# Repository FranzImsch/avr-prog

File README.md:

# AVR-Prog
Basic Programmer for AVR-Chips. It's based off the [Sparkfun Tiny AVR Programmer](https://github.com/sparkfun/Tiny-AVR-Programmer).

Features are:
- USB-C connector,
- 5V or 3V3 logic level,
- Tag-Connect connector.

## Partlist

|Name     |Component             |Package                |
|---------|----------------------|-----------------------|
|C1, C3   |100nF Cap             |0603                   |
|C2       |10µF Cap              |0603                   |
|C4, C5   |2.2µF Cap             |0603                   |
|C6, C9   |18pF Cap              |0603                   |
|IC1      |ATTINY84A-SSU         |SOIC127P600X175-14N    |
|J1       |JUMPER 3x 1.27mm      |                       |
|J3       |Box Header 6P         |                       |
|LED      |LED                   |0603                   |
|R1       |1K Resistor           |0402                   |
|R2, R9   |68Ω Resistor          |0402                   |
|R3       |1K5 Resistor          |0402                   |
|R4       |10KΩ Resistor         |0603                   |
|R6, R7   |5K1 Resistor          |0402                   |
|R8       |10K Resistor          |0402                   |
|U$1      |USB-C Connector       |TYPE-C16PIN            |
|U$2      |TLV75533PDBVR         |SOT23-5                |
|U$3      |SRV05-4-P-T7          |SOT23-6                |
|X1       |KMD160001210          |M-49USSMD              |

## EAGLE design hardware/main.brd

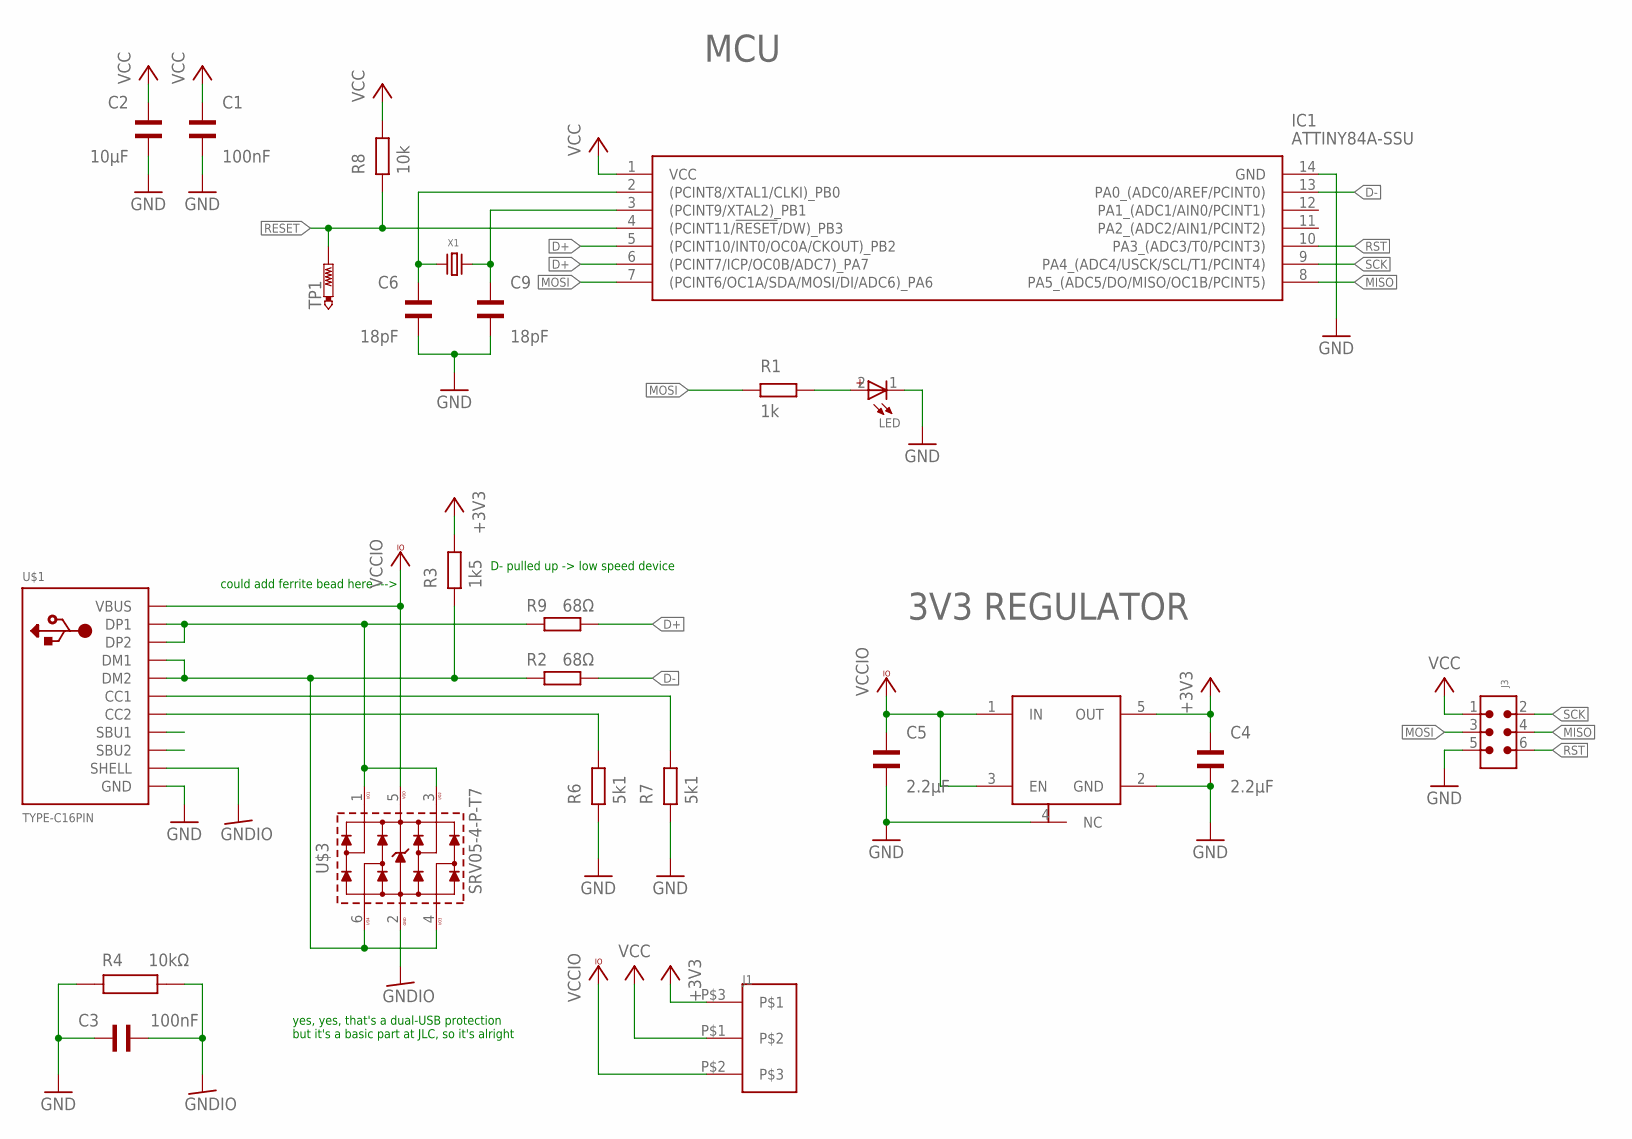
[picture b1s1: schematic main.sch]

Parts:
C1, C3: 100nF; WCAP-CSGP_0603_REFLOW
C2: 10µF; WCAP-CSGP_0603_REFLOW
C4, C5: 2.2µF; WCAP-CSGP_0603_REFLOW
C6, C9: 18pF; WCAP-CSGP_0603_REFLOW
IC1: ATTINY84A-SSU; SOIC127P600X175-14N
J1: JUMPER1.27; 1.27_JUMPER
J3: 6120XX21621_61200621621; 61200621621
LED: WL-SMCW_0603_150060GS75000; WL-SMCW_0603
R1: 1k; WRIS-KSKE_0402
R2, R9: 68Ω; WRIS-KSKE_0402
R3: 1k5; WRIS-KSKE_0402
R4: 10kΩ; WRIS-PSMB_0603_1.6X0.8X0.35X0.6(LXWXHXPW)
R6, R7: 5k1; WRIS-KSKE_0402
R8: 10k; WRIS-KSKE_0402
TP1: PTR1B1,27; B1,27
U$1: TYPE-C16PIN
U$2: TLV75533PDBVRSOT-23-5; DBV_R-PDSO-G5
U$3: SRV05-4-P-T7; SOT23-6
X1: KMD160001210; M-49USSMD

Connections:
+3V3: C4.2, J1.P$3, R3.2, U$2.5 (OUT)
D+: IC1.5 ((PCINT10/INT0/OC0A/CKOUT)_PB2), IC1.6 ((PCINT7/ICP/OC0B/ADC7)_PA7), R9.2
D+_RAW: R9.1, U$1.A6 (DP1), U$1.B6 (DP2), U$3.1 (IO1), U$3.3 (IO2)
D-: IC1.13 (PA0_(ADC0/AREF/PCINT0)), R2.2
D-_RAW: R2.1, R3.1, U$1.A7 (DM1), U$1.B7 (DM2), U$3.4 (IO3), U$3.6 (IO4)
GND: C1.1, C2.1, C3.2, C4.1, C5.1, C6.1, C9.1, IC1.14 (GND), J3.5, LED.1 (-), R4.1, R6.1, R7.1, U$1.A1B12 (GND), U$1.B1A12 (GND), U$2.2 (GND), U$2.4 (NC)
GNDIO: C3.1, R4.2, U$1.SHELL1 (SHELL), U$1.SHELL2 (SHELL), U$1.SHELL3 (SHELL), U$1.SHELL4 (SHELL), U$3.2 (GND)
MISO: IC1.8 (PA5_(ADC5/DO/MISO/OC1B/PCINT5)), J3.4
MOSI: IC1.7 ((PCINT6/OC1A/SDA/MOSI/DI/ADC6)_PA6), J3.3, R1.1
unnamed: LED.2 (+), R1.2
unnamed: R7.2, U$1.A5 (CC1)
unnamed: R6.2, U$1.B5 (CC2)
unnamed: C6.2, IC1.2 ((PCINT8/XTAL1/CLKI)_PB0), X1.P$1 (1)
unnamed: C9.2, IC1.3 ((PCINT9/XTAL2)_PB1), X1.P$2 (2)
RESET: IC1.4 ((PCINT11/!RESET!/DW)_PB3), R8.1, TP1.TP
RST: IC1.10 (PA3_(ADC3/T0/PCINT3)), J3.6
SCK: IC1.9 (PA4_(ADC4/USCK/SCL/T1/PCINT4)), J3.2
VCC: C1.2, C2.2, IC1.1 (VCC), J1.P$1, J3.1, R8.2
VCCIO: C5.2, J1.P$2, U$1.A4B9 (VBUS), U$1.B4A9 (VBUS), U$2.1 (IN), U$2.3 (EN), U$3.5 (VDD)

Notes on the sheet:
MCU
3V3 REGULATOR
yes, yes, that's a dual-USB protection but it's a basic part at JLC, so it's alright
could add ferrite bead here --->
D- pulled up -> low speed device

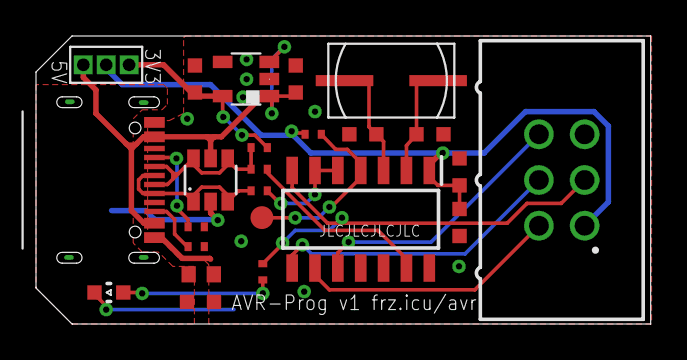
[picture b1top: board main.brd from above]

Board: 2 copper layers, 34.1 x 16.0 mm, 24 parts (0 on the bottom side), 19 nets.

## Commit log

2020-10-13 initialising repo
2020-10-16 v1.0
2020-10-18 fixed partlist
2020-10-19 added assembly guide

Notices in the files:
parts and their libraries:
885012206052_Eagle_WCAP-CSGP_rev19b: Copyright: Würth Elektronik
